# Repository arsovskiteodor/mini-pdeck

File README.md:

# Minipad

A small USB macropad: 4 low-profile keys with white backlight LEDs, 2 rotary encoders with push buttons and a
0.96" OLED, on a custom 2-layer PCB, running QMK.

It's my first PCB, built as a learning project that covers the whole path from a blank page to a working
board: requirements, part selection, schematic and layout in KiCad 10, ordering from a fab, hand assembly,
bring-up and firmware. The goal was to understand each step well enough to design the next board alone.

## Status
**Rev A is fully assembled and every input and output works.**

| | |
|---|---|
| Rev A ordered | 2026-11-03, PCBWay |
| Arrived, assembled | 2026-11-13; 2026-11-14 (all but the encoders), encoders 2026-11-19 |
| Tested on the board | 2026-11-14: all 4 keys type; all 4 key LEDs breathe (hardware PWM); OLED shows a status screen. 2026-11-19: both encoders turn and push (volume/mute, arrows/Enter), counted on the OLED |
| Next | VIA remapping, the case, and a Rev B with the lessons from Rev A |

Day-to-day state, open questions and next actions: [STATUS.md](STATUS.md).

## Hardware
| Part | Choice | Why (ADR) |
|---|---|---|
| MCU | RP2040-Zero (clone), soldered on as a module | [0001](docs/decisions/0001-mcu-rp2040-zero-module.md) |
| Switches | Gateron KS-33 Low Profile 2.0, soldered | [0002](docs/decisions/0002-switches-gateron-ks33-low-profile.md) |
| Key LEDs | White 1206 LEDs under the switches, hand-soldered | [0009](docs/decisions/0009-fab-tht-plus-hand-soldered-1206-leds.md) |
| Encoders | Bourns PEC11L-4115F-S0020, with push switch | [0013](docs/decisions/0013-encoders-bourns-pec11l-4115f.md) |
| Display | 0.96" 128 × 64 SSD1306, I2C | [0004](docs/decisions/0004-oled-ssd1306-i2c.md) |
| Wiring | One GPIO per input, no matrix | [0006](docs/decisions/0006-direct-pin-wiring.md) |
| PCB | 2 layers, 69.8 × 69.1 mm, through-hole except the LEDs, PCBWay | [0012](docs/decisions/0012-fab-pcbway-instead-of-jlcpcb.md) |
| Mounting | Four M3 holes, one per corner | [0010](docs/decisions/0010-m3-mounting-holes-at-the-corners.md) |
| Firmware | QMK, with VIA for remapping, own PC app later | [0005](docs/decisions/0005-firmware-qmk.md), [0008](docs/decisions/0008-remapping-via-then-own-app.md) |

Parts list with sources and verification: [docs/hardware/parts.md](docs/hardware/parts.md).
GPIO allocation: [docs/hardware/pinout.md](docs/hardware/pinout.md).

## How the project is run
The work follows 13 steps in 4 phases ([docs/phases/](docs/phases/)). Each step has an exit criterion that
has to be met before the next one starts.

- **Decisions** are written down as ADRs ([docs/decisions/](docs/decisions/)): the context, the real
  alternatives, what was chosen and what was rejected. When I changed my mind, I wrote a new ADR instead of
  editing the old one, for example when the encoders changed from generic EC11s to Bourns (0003 → 0013) and
  the fab from JLCPCB to PCBWay (0012, superseding 0009).
- **Every dimension cites a source:** a datasheet page or a measurement on the real part. Otherwise it says
  `TBD`. The parts are clones and generics, so the original datasheets are a starting point, not proof.
- **A log per working day** ([docs/log/](docs/log/)), append-only: mistakes are corrected in a later entry,
  not erased.
- Rev A was ordered **before** every footprint was verified against the real parts, as a deliberate
  trade-off ([ADR-0011](docs/decisions/0011-order-rev-a-before-parts-verification.md)).

## How I used AI
I used [Claude Code](https://claude.com/claude-code) as a mentor throughout, and the setup is part of this
repository: the commands and rules in [`.claude/`](.claude/) and the logs show what it did and what I did.

- **What I did:** made or approved every decision (the ADRs record the alternatives, the reasons, and who proposed what); drew the schematic;
  placed and routed the PCB; ordered the boards; assembled and soldered Rev A; flashed it and tested every
  fitted part.
- **What Claude did:** explained each step before I did it; reviewed my schematic and layout; read datasheets
  and part listings with me and checked them against the requirements; drafted most of the documentation
  (ADRs, logs and this README); and wrote parts of the firmware, which I tested on the board.
- **The rules it worked under:** no dimension, pinout or limit from memory (cite a source or write `TBD`);
  hardware results are recorded only as reported by me, with the date; it never places orders, and
  commits or pushes only when I ask.

Commands used in sessions:

| Command | When |
|---|---|
| `/where-are-we` | Start of a session: recap and next step |
| `/check-part <part>` | Evaluating a listing, or when a part arrives |
| `/decision <title>` | After choosing between real alternatives (writes an ADR) |
| `/gate` | When a step's exit criterion looks met |
| `/pre-order` | Before ordering the PCB |
| `/log-session` | End of a session: log entry and STATUS update |

## Building it yourself
**Hardware:** open [`hardware/kicad/mini-pdeck.kicad_pro`](hardware/kicad/) in KiCad 10. The libraries are
project-local, so nothing needs installing. Checks:
```sh
kicad-cli sch erc -o hardware/kicad/production/erc.rpt hardware/kicad/mini-pdeck.kicad_sch
kicad-cli pcb drc -o hardware/kicad/production/drc.rpt hardware/kicad/mini-pdeck.kicad_pcb
```
Rev A has known issues and unverified footprints (see [STATUS.md](STATUS.md) and
[docs/hardware/parts.md](docs/hardware/parts.md)). Check them before ordering a copy.

**Firmware:** set up QMK and link the keyboard folder as described in
[firmware/README.md](firmware/README.md), then build:
```sh
qmk compile -kb minipad -km default
```
(On this project's Windows PC, QMK runs in WSL: `wsl bash firmware/build.sh` builds and copies the `.uf2`
to `firmware/out/`.)
Flash: hold BOOT on the RP2040-Zero, plug it in, and copy the `.uf2` onto the `RPI-RP2` drive.

## Repository layout
```
.
├── README.md, STATUS.md      # Overview; current state and open questions
├── LICENSE.md, LICENSES/     # Which licence covers what, and the full texts
├── .claude/                  # Claude Code setup: permissions, rules, commands, review agent
├── docs/
│   ├── phases/               # The 13 steps in 4 phases, with exit criteria
│   ├── decisions/            # ADRs: what was chosen, what was rejected and why
│   ├── log/                  # One file per working day, append-only
│   └── hardware/             # Parts, pinout, mechanical, fabrication, bring-up, datasheet links
├── hardware/kicad/           # KiCad 10 project and project-local libraries
├── firmware/
│   ├── qmk/minipad/          # QMK keyboard definition and keymap
│   ├── bench/                # Arduino sketches used to test the OLED and an encoder before the PCB
│   └── build.sh              # Build in WSL and copy the .uf2 to firmware/out/
└── case/                     # Enclosure (not started)
```

## Licence
Hardware: [CERN-OHL-P-2.0](LICENSES/CERN-OHL-P-2.0.txt). Firmware: [GPL-2.0-or-later](LICENSES/GPL-2.0-or-later.txt).
Documentation: [CC-BY-4.0](LICENSES/CC-BY-4.0.txt). Some library files come from other projects and keep their
own licence. Details: [LICENSE.md](LICENSE.md).

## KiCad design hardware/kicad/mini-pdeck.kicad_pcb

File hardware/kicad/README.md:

# KiCad project

Created with KiCad 10 (draft schematic, 2026-10-30), named `mini-pdeck`: `mini-pdeck.kicad_pro`,
`mini-pdeck.kicad_sch` and `mini-pdeck.kicad_pcb`, directly in this folder. Keep them here: `${KIPRJMOD}`
(the project folder) is how the library table and the 3D model links find `lib/`.

## Libraries
Libraries are project-local, so the repo works on any machine without changing global KiCad settings.

```
hardware/kicad/
├── lib/
│   ├── minipad.pretty/         # OUR footprints: every one verified against a real part
│   ├── minipad.kicad_sym       # OUR symbols (if any are needed)
│   └── third_party/
│       └── key-switches.pretty # git submodule, never edited
└── production/                 # fab outputs, gitignored
```

- Add the switch library as a submodule:
  `git submodule add https://github.com/siderakb/key-switches.pretty hardware/kicad/lib/third_party/key-switches.pretty`
- Register libraries in **Preferences → Manage Footprint Libraries → Project Specific Libraries**
  with paths like `${KIPRJMOD}/lib/minipad.pretty`.
- **Copy before you change.** To use or tweak a third-party or stock footprint, copy it into
  `minipad.pretty` first. Note its source and verification status in `docs/hardware/parts.md`.

## Footprint sources (starting points, all to be verified in step 07)
| Part | Starting footprint | Verify against |
|---|---|---|
| RP2040-Zero | Candidate: `minipad.pretty/MODULE_RP2040-ZERO`, SnapMagic copy with the Waveshare 3D model added (`parts.md`, U1). Final choice in step 07 | Waveshare drawing and the measured clone |
| Gateron KS-33 | `minipad.pretty/SW_Gateron_LowProfile_THT`: copy of `key-switches.pretty` (soldered, Q1) with Gateron's 3D model added (`lib/3d/`, gitignored). Checked against the Gateron drawing (`parts.md`, SW1–SW4) | Real switch, 1:1 print |
| White LED 1206 (D1–D4, ADR-0009) | `minipad.pretty/LED_1206_3216Metric_Pad1.42x1.75mm_HandSolder`: unchanged copy of KiCad 10 stock | Pads inside the switch's LED window (`parts.md`, D1–D4); real LED with calipers |
| EC11 | `minipad.pretty/RotaryEncoder_Alps_EC11E-Switch_Vertical_H20mm`: copy of KiCad 10 stock with a Bourns PEC11R 3D model as stand-in (`lib/3d/`, gitignored). Pin hole and tab slots differ from the SR Passives drawing (`parts.md`, ENC1–ENC2) | Real encoder, 1:1 print |
| OLED | Now: KiCad 10 stock `Connector_PinHeader_2.54mm:PinHeader_1x04_P2.54mm_Vertical`, linked straight from the stock library (owner, 2026-10-31; an identical copy sits unused in `minipad.pretty`). The module's header is soldered in, no socket. Later: our own footprint with the module outline, and mounting holes if chosen (Q7), from calipers | Received module (pin order!) |
| Resistors R1–R6 (pull-ups, LED series) | `minipad.pretty/R_Axial_DIN0207_L6.3mm_D2.5mm_P7.62mm_Horizontal`: unchanged copy of KiCad 10 stock (1/4 W, body 6.3 × Ø2.5 mm, 7.62 mm pitch, 0.8 mm drill) | Real resistor: body size and lead diameter with calipers |

## Habits
- Commit after each milestone: schematic done, footprints assigned, placement done, routing done.
  These give you restore points.
- Run ERC and DRC often, not just at the end.
- Don't hand-edit `.kicad_sch` or `.kicad_pcb` text files. Make changes in KiCad.

## Licences of library files
The project's own design files are CERN-OHL-P-2.0 (`LICENSE.md` at the repo root). Library files copied
from elsewhere keep their upstream licence. Full texts are in `LICENSES/`.

| File | Upstream | Licence |
|---|---|---|
| `minipad.pretty/SW_Gateron_LowProfile_THT` | `siderakb/key-switches.pretty`, commit `e7dea70` (`parts.md`, SW1–SW4) | CERN-OHL-P-2.0 |
| `minipad.pretty/MODULE_RP2040-ZERO` | SnapMagic RP2040-ZERO (`third_party/snapmagic-RP2040-ZERO/README.md`) | CC-BY-SA-4.0 with SnapMagic Design Exception 1.0 |
| `minipad.pretty/LED_1206_…`, `R_Axial_…`, `PinHeader_1x04_…`, `RotaryEncoder_Alps_EC11E-…` | KiCad 10 stock libraries | CC-BY-SA-4.0 with the KiCad library exception (https://www.kicad.org/libraries/license/) |
| `third_party/snapmagic-RP2040-ZERO/` | SnapMagic | CC-BY-SA-4.0 with Design Exception 1.0 |
| `third_party/bobu01-RP2040-Zero-Kicad-Footprint-1mm/` | bobu01 on GitHub | GPL-3.0 (its own `LICENSE`) |

Both exceptions say the same thing: a board design that *uses* these footprints is not bound by
CC BY-SA, so the board can be CERN-OHL-P. The footprint files themselves stay CC BY-SA.

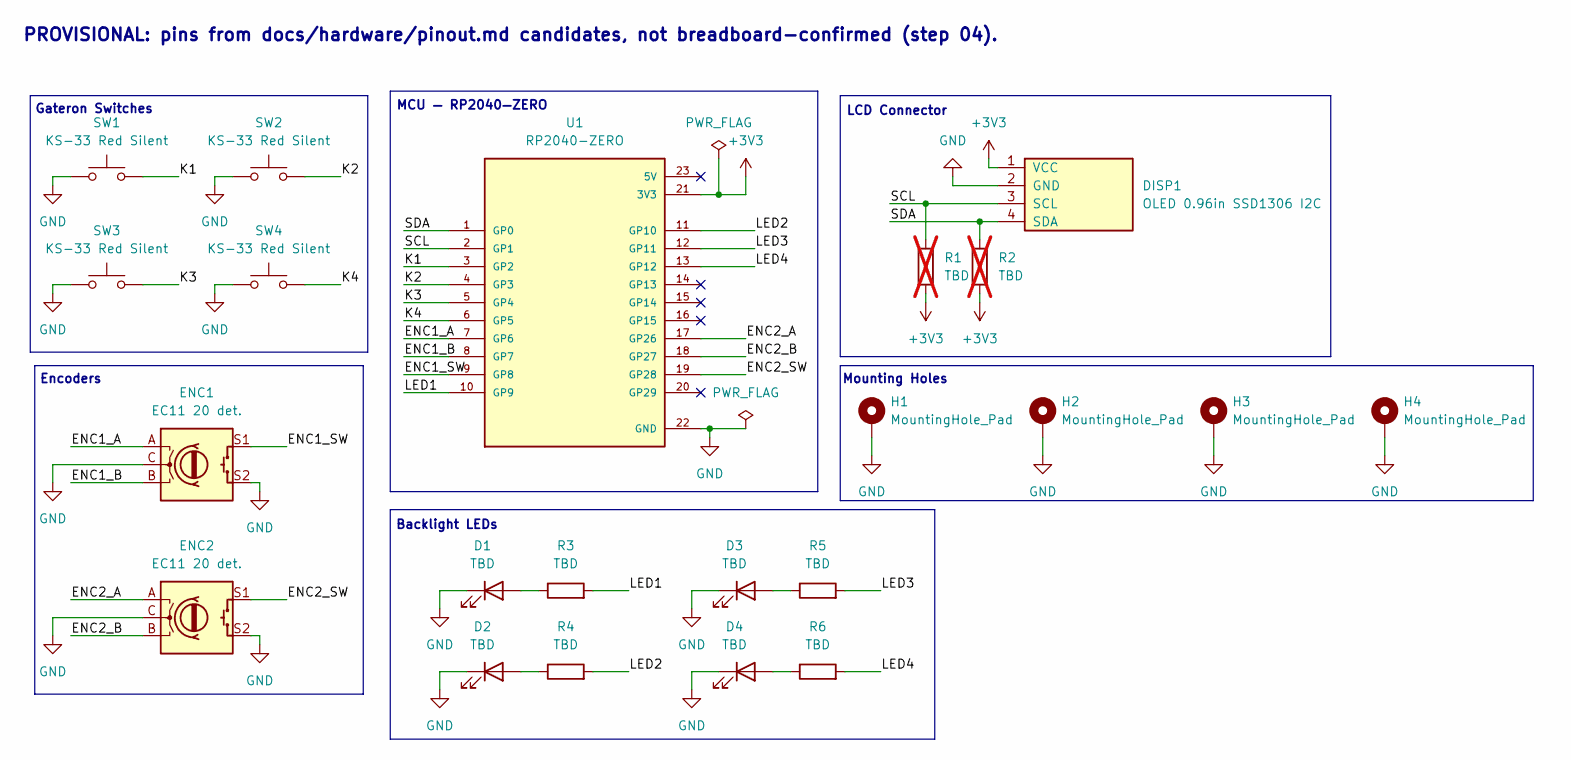
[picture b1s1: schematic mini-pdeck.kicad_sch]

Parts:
D1, D2, D3, D4: TBD; LED_1206_3216Metric_Pad1.42x1.75mm_HandSolder
DISP1: OLED 0.96in SSD1306 I2C; PinHeader_1x04_P2.54mm_Vertical
ENC1, ENC2: EC11 20 det.; RotaryEncoder_Alps_EC11E-Switch_Vertical_H20mm
H1, H2, H3, H4: MountingHole_Pad; MountingHole_3.2mm_M3_Pad
R1, R2: TBD; R_Axial_DIN0207_L6.3mm_D2.5mm_P7.62mm_Horizontal; not fitted
R3, R4, R5, R6: TBD; R_Axial_DIN0207_L6.3mm_D2.5mm_P7.62mm_Horizontal
SW1, SW2, SW3, SW4: KS-33 Red Silent; SW_Gateron_LowProfile_THT
U1: RP2040-ZERO; MODULE_RP2040-ZERO; PARTREV NA

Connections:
+3V3: DISP1.1 (VCC), R1.2, R2.2, U1.21 (3V3)
/ENC1_A: ENC1.A, U1.7 (GP6)
/ENC1_B: ENC1.B, U1.8 (GP7)
/ENC1_SW: ENC1.S1, U1.9 (GP8)
/ENC2_A: ENC2.A, U1.17 (GP26)
/ENC2_B: ENC2.B, U1.18 (GP27)
/ENC2_SW: ENC2.S1, U1.19 (GP28)
/K1: SW1.2, U1.3 (GP2)
/K2: SW2.2, U1.4 (GP3)
/K3: SW3.2, U1.5 (GP4)
/K4: SW4.2, U1.6 (GP5)
/LED1: R3.2, U1.10 (GP9)
/LED2: R4.2, U1.11 (GP10)
/LED3: R5.2, U1.12 (GP11)
/LED4: R6.2, U1.13 (GP12)
/SCL: DISP1.3 (SCL), R1.1, U1.2 (GP1)
/SDA: DISP1.4 (SDA), R2.1, U1.1 (GP0)
GND: D1.1 (K), D2.1 (K), D3.1 (K), D4.1 (K), DISP1.2 (GND), ENC1.C, ENC1.S2, ENC2.C, ENC2.S2, H1.1 (1_1), H2.1 (1_1), H3.1 (1_1), H4.1 (1_1), SW1.1, SW2.1, SW3.1, SW4.1, U1.22 (GND)
unnamed: D1.2 (A), R3.1
unnamed: D2.2 (A), R4.1
unnamed: D3.2 (A), R5.1
unnamed: D4.2 (A), R6.1

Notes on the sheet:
Encoders
MCU — RP2040—ZERO
PROVISIONAL: pins from docs/hardware/pinout.md candidates, not breadboard-confirmed (step 04).
Mounting Holes
LCD Connector
Backlight LEDs
Gateron Switches

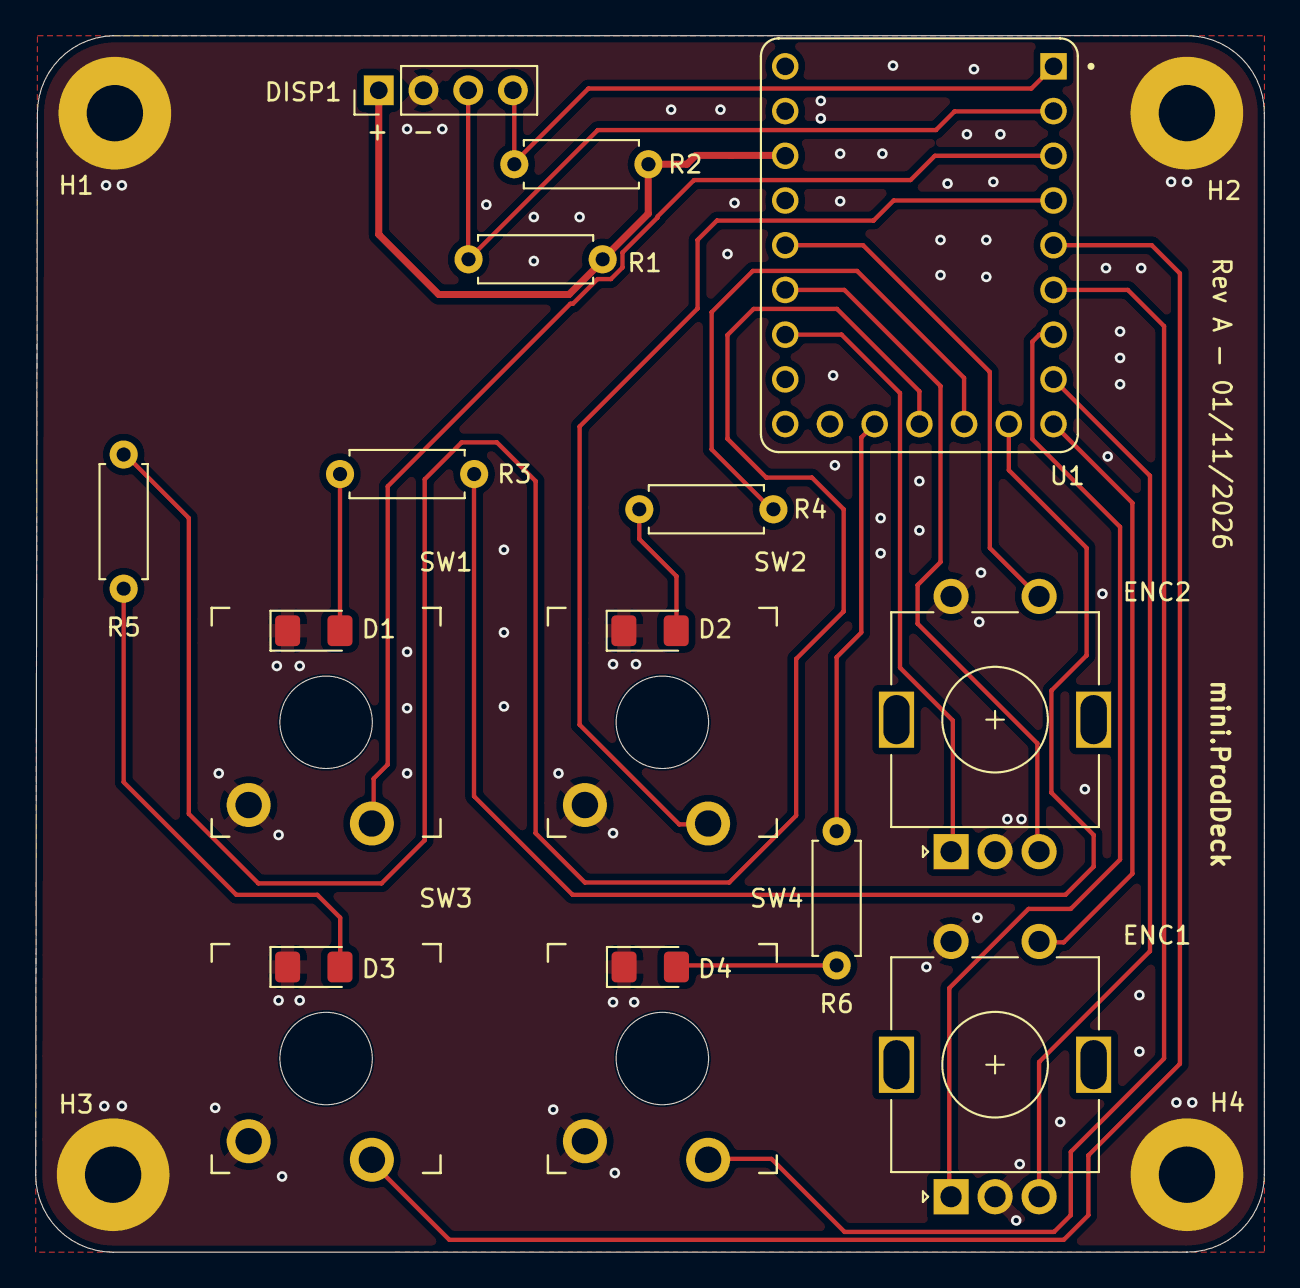
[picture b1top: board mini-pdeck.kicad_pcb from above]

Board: 2 copper layers, 69.8 x 69.1 mm, 22 parts (0 on the bottom side), 22 nets.
